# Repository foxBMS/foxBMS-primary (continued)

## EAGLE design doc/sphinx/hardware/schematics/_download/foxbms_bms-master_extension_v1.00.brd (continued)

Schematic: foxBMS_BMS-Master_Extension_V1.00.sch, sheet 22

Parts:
JP2201, JP2202: PINHD-2X12; 2X12

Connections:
+3.3V_0: JP2201.1, JP2201.3, JP2202.1, JP2202.3; also elsewhere on the board
ADC_MCU_0_CH_0: JP2202.8; also elsewhere on the board
ADC_MCU_0_CH_1: JP2202.7; also elsewhere on the board
ADC_MCU_0_CH_2: JP2202.6; also elsewhere on the board
ADC_MCU_0_CH_3: JP2202.5; also elsewhere on the board
ADC_MCU_0_CH_4: JP2202.9; also elsewhere on the board
CAN_1_RX: JP2201.6; also elsewhere on the board
CAN_1_TRANS_STANDBY_CONTROL: JP2201.5; also elsewhere on the board
CAN_1_TX: JP2201.7; also elsewhere on the board
CONTACTOR_6_CONTROL: JP2201.18; also elsewhere on the board
CONTACTOR_6_FEEDBACK: JP2201.17; also elsewhere on the board
CONTACTOR_7_CONTROL: JP2201.16; also elsewhere on the board
CONTACTOR_7_FEEDBACK: JP2201.15; also elsewhere on the board
CONTACTOR_8_CONTROL: JP2202.10; also elsewhere on the board
CONTACTOR_8_FEEDBACK: JP2202.11; also elsewhere on the board
DATA_STORAGE_SPI_MISO: JP2201.21; also elsewhere on the board
DATA_STORAGE_SPI_MOSI: JP2201.19; also elsewhere on the board
DATA_STORAGE_SPI_SCK: JP2201.20; also elsewhere on the board
DATA_STORAGE_SPI_SDCARD_NSS: JP2201.23; also elsewhere on the board
GND_0: JP2201.2, JP2201.4, JP2202.2, JP2202.4; also elsewhere on the board
ISONOC_0_CONTROL: JP2202.16; also elsewhere on the board
ISONOC_1_CONTROL: JP2202.17; also elsewhere on the board
ISONOC_2_CONTROL: JP2202.18; also elsewhere on the board
ISONOC_3_CONTROL: JP2202.19; also elsewhere on the board
ISONOC_4_CONTROL: JP2202.20; also elsewhere on the board
ISONOC_5_CONTROL: JP2202.21; also elsewhere on the board
ISO_GPIO_MCU_0_IN_0: JP2202.22; also elsewhere on the board
ISO_GPIO_MCU_0_IN_1: JP2202.23; also elsewhere on the board
ISO_GPIO_MCU_0_IN_2: JP2201.13; also elsewhere on the board
ISO_GPIO_MCU_0_IN_3: JP2201.10; also elsewhere on the board
ISO_GPIO_MCU_0_OUT_0: JP2201.9; also elsewhere on the board
ISO_GPIO_MCU_0_OUT_1: JP2201.14; also elsewhere on the board
ISO_GPIO_MCU_0_OUT_2: JP2201.11; also elsewhere on the board
ISO_GPIO_MCU_0_OUT_3: JP2201.12; also elsewhere on the board
RS485_MCU_0_DE: JP2202.15; also elsewhere on the board
RS485_MCU_0_NRE: JP2202.14; also elsewhere on the board
RS485_MCU_0_RX: JP2202.13; also elsewhere on the board
RS485_MCU_0_TX: JP2202.12; also elsewhere on the board
SDCARD_SUPPLY_CONTROL: JP2201.22; also elsewhere on the board

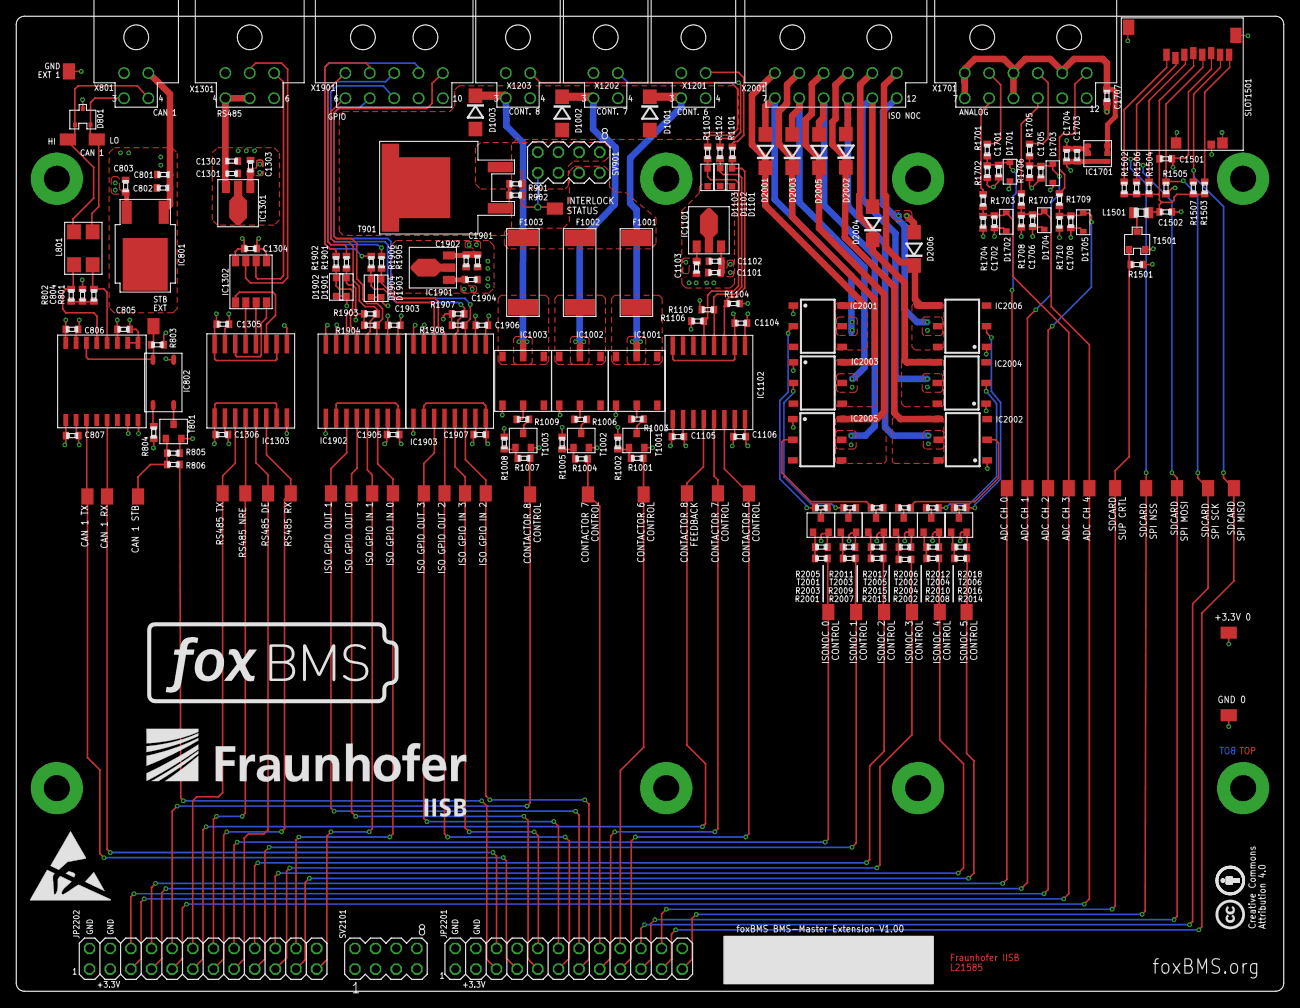
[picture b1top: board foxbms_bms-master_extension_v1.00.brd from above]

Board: 4 copper layers, 156.0 x 120.0 mm, 220 parts (0 on the bottom side), 141 nets.

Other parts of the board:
U$1: ESD_10.00

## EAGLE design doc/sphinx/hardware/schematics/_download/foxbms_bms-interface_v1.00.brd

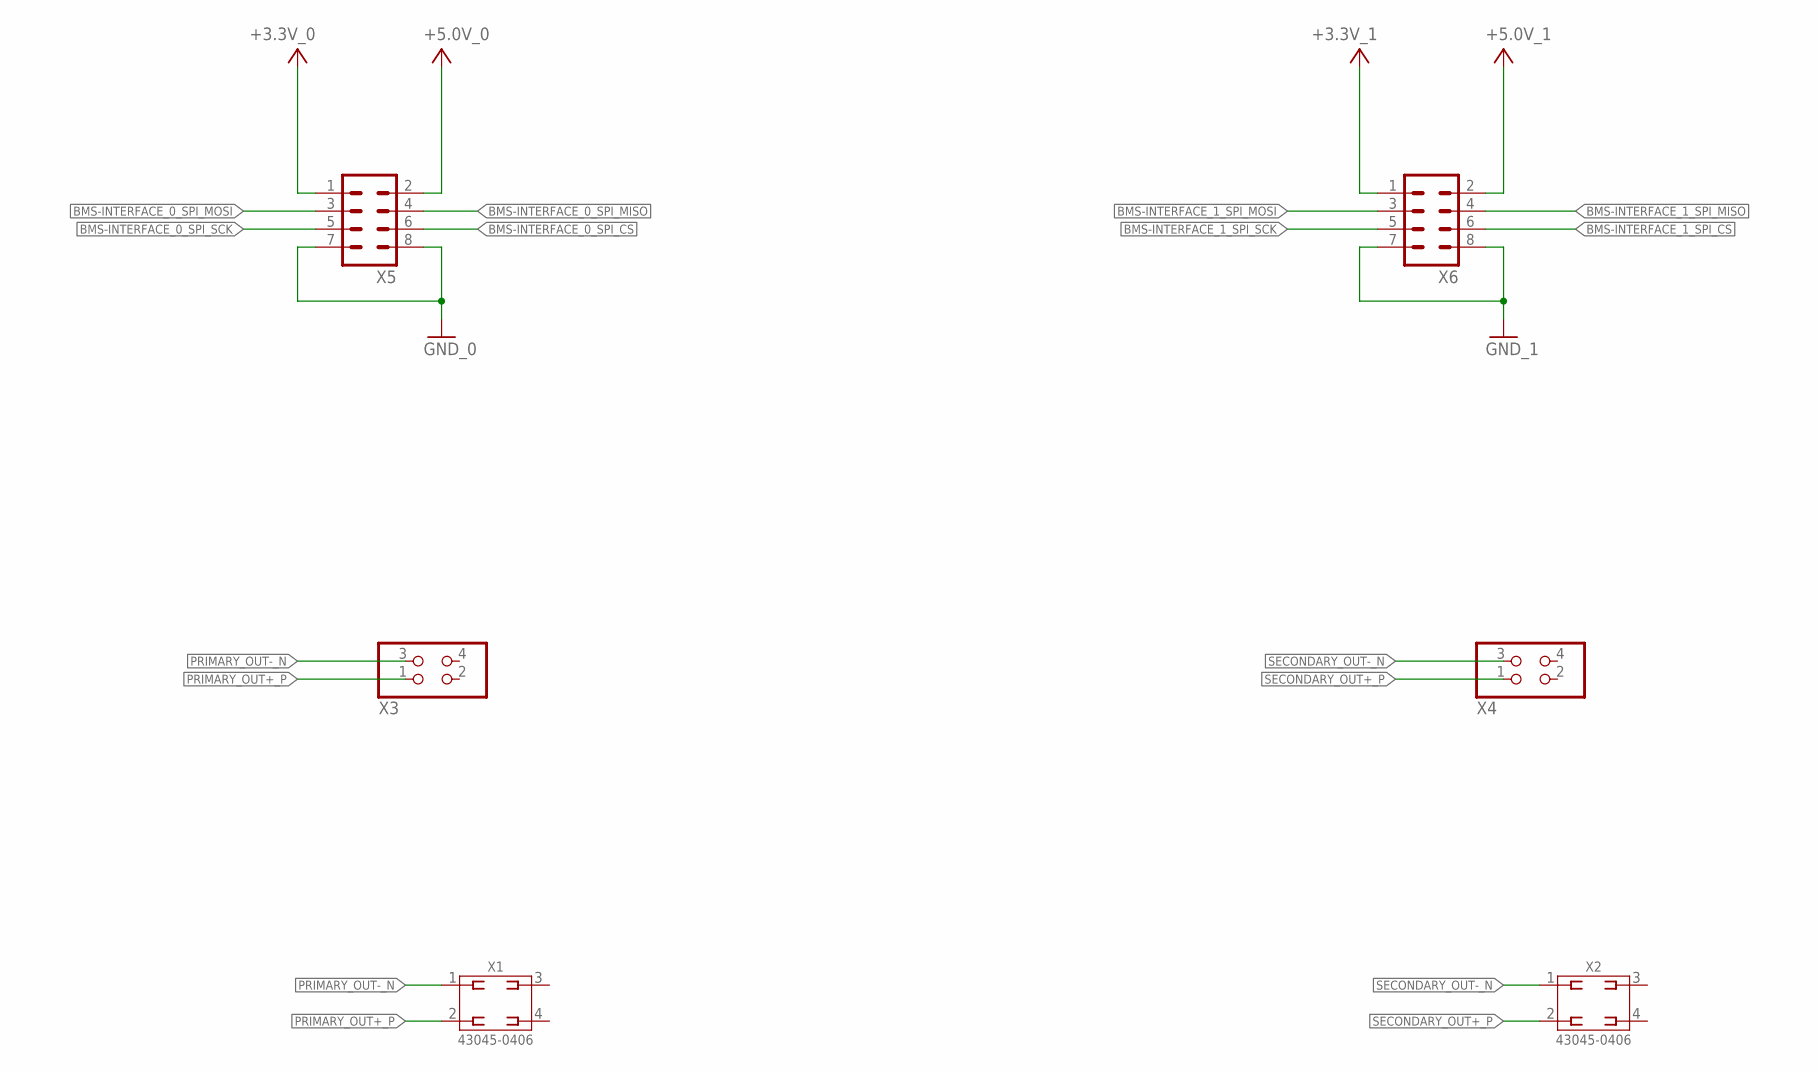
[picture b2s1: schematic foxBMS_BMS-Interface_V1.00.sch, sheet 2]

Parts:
X1, X2: 43045-0406_MOLEX_4PIN; X_SMD_MOLEX_43045-0408_R_REV01
X3, X4: PINHD-2X2; 2X02
X5, X6: MA04-2

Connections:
+3.3V_0: X5.1; also elsewhere on the board
+3.3V_1: X6.1; also elsewhere on the board
+5.0V_0: X5.2
+5.0V_1: X6.2
BMS-INTERFACE_0_SPI_CS: X5.6; also elsewhere on the board
BMS-INTERFACE_0_SPI_MISO: X5.4; also elsewhere on the board
BMS-INTERFACE_0_SPI_MOSI: X5.3; also elsewhere on the board
BMS-INTERFACE_0_SPI_SCK: X5.5; also elsewhere on the board
BMS-INTERFACE_1_SPI_CS: X6.6; also elsewhere on the board
BMS-INTERFACE_1_SPI_MISO: X6.4; also elsewhere on the board
BMS-INTERFACE_1_SPI_MOSI: X6.3; also elsewhere on the board
BMS-INTERFACE_1_SPI_SCK: X6.5; also elsewhere on the board
GND_0: X5.7, X5.8; also elsewhere on the board
GND_1: X6.7, X6.8; also elsewhere on the board
PRIMARY_OUT+_P: X1.2, X3.1; also elsewhere on the board
PRIMARY_OUT-_N: X1.1, X3.3; also elsewhere on the board
SECONDARY_OUT+_P: X2.2, X4.1; also elsewhere on the board
SECONDARY_OUT-_N: X2.1, X4.3; also elsewhere on the board

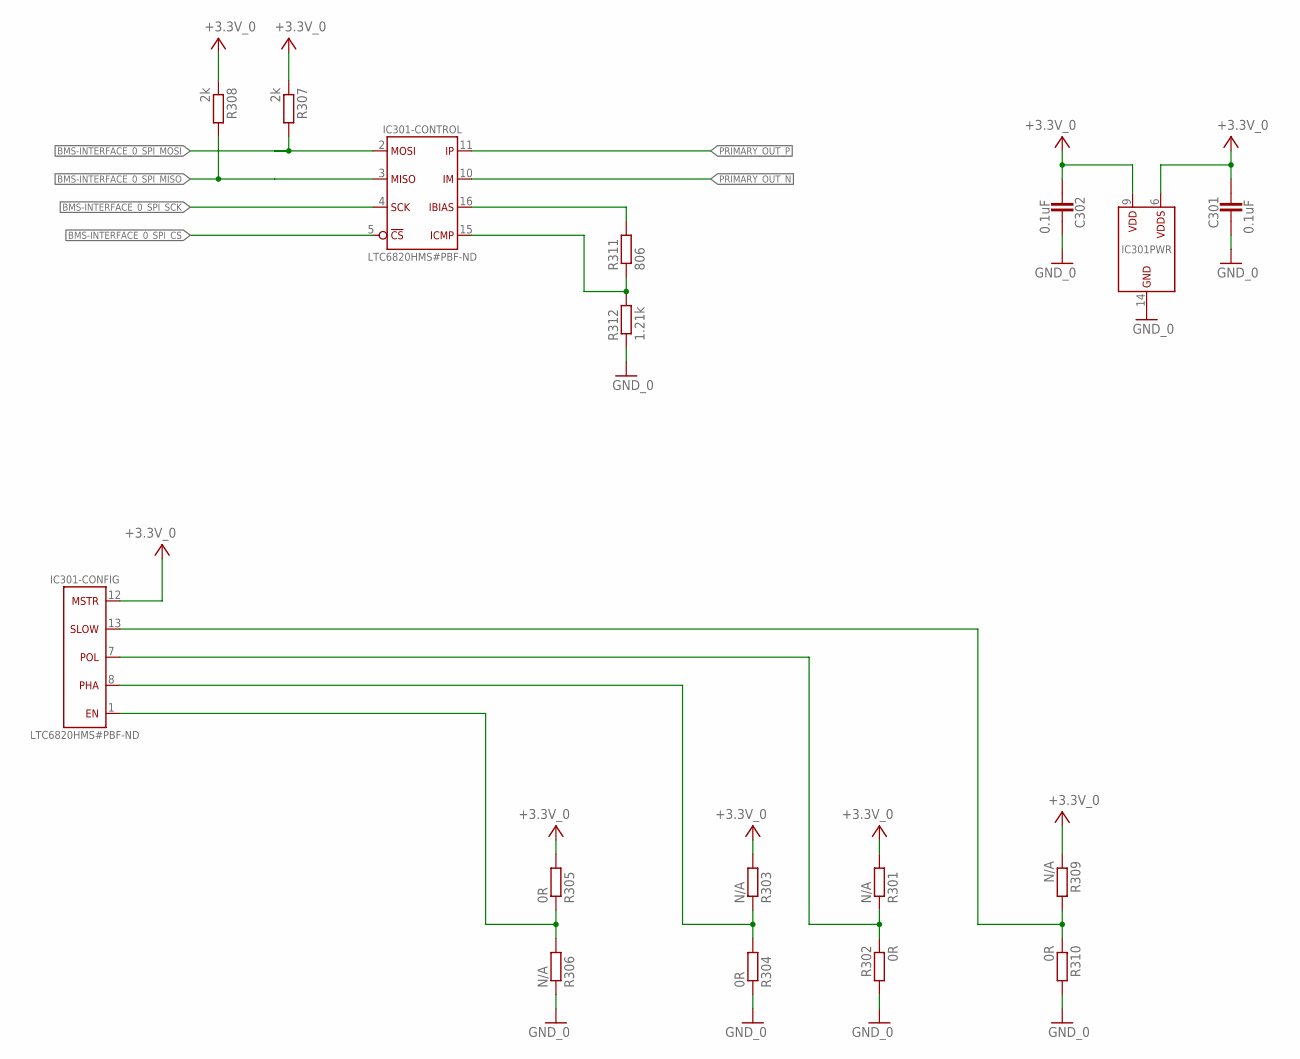
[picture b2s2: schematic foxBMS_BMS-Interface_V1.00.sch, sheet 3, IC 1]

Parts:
C301, C302: 0.1uF; 0603
IC301: LTC6820HMS#PBF; IC_SMD_MSOP-16_(MS16)_R_LINEAR_REV01
R301, R303, R306, R309: N/A; 0603
R302, R304, R305, R310: 0R; 0603
R307, R308: 2k; 0603
R311: 806; 0603
R312: 1.21k; 0603

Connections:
+3.3V_0: C301.2, C302.2, IC301.6 (VDDS), IC301.9 (VDD), IC301.12 (MSTR), R301.2, R303.2, R305.2, R307.1, R308.1, R309.1; also elsewhere on the board
BMS-INTERFACE_0_SPI_CS: IC301.5 (!CS); also elsewhere on the board
BMS-INTERFACE_0_SPI_MISO: IC301.3 (MISO), R308.2; also elsewhere on the board
BMS-INTERFACE_0_SPI_MOSI: IC301.2 (MOSI), R307.2; also elsewhere on the board
BMS-INTERFACE_0_SPI_SCK: IC301.4 (SCK); also elsewhere on the board
EN-BACKUP: IC301.1 (EN), R305.1, R306.2
GND_0: C301.1, C302.1, IC301.14 (GND), R302.2, R304.1, R306.1, R310.2, R312.1; also elsewhere on the board
unnamed: IC301.16 (IBIAS), R311.2
unnamed: IC301.15 (ICMP), R311.1, R312.2
PHA-PRIMARY: IC301.8 (PHA), R303.1, R304.2
POL-PRIMARY: IC301.7 (POL), R301.1, R302.1
PRIMARY_OUT_N: IC301.10 (IM); also elsewhere on the board
PRIMARY_OUT_P: IC301.11 (IP); also elsewhere on the board
SLOW-PRIMARY: IC301.13 (SLOW), R309.2, R310.1

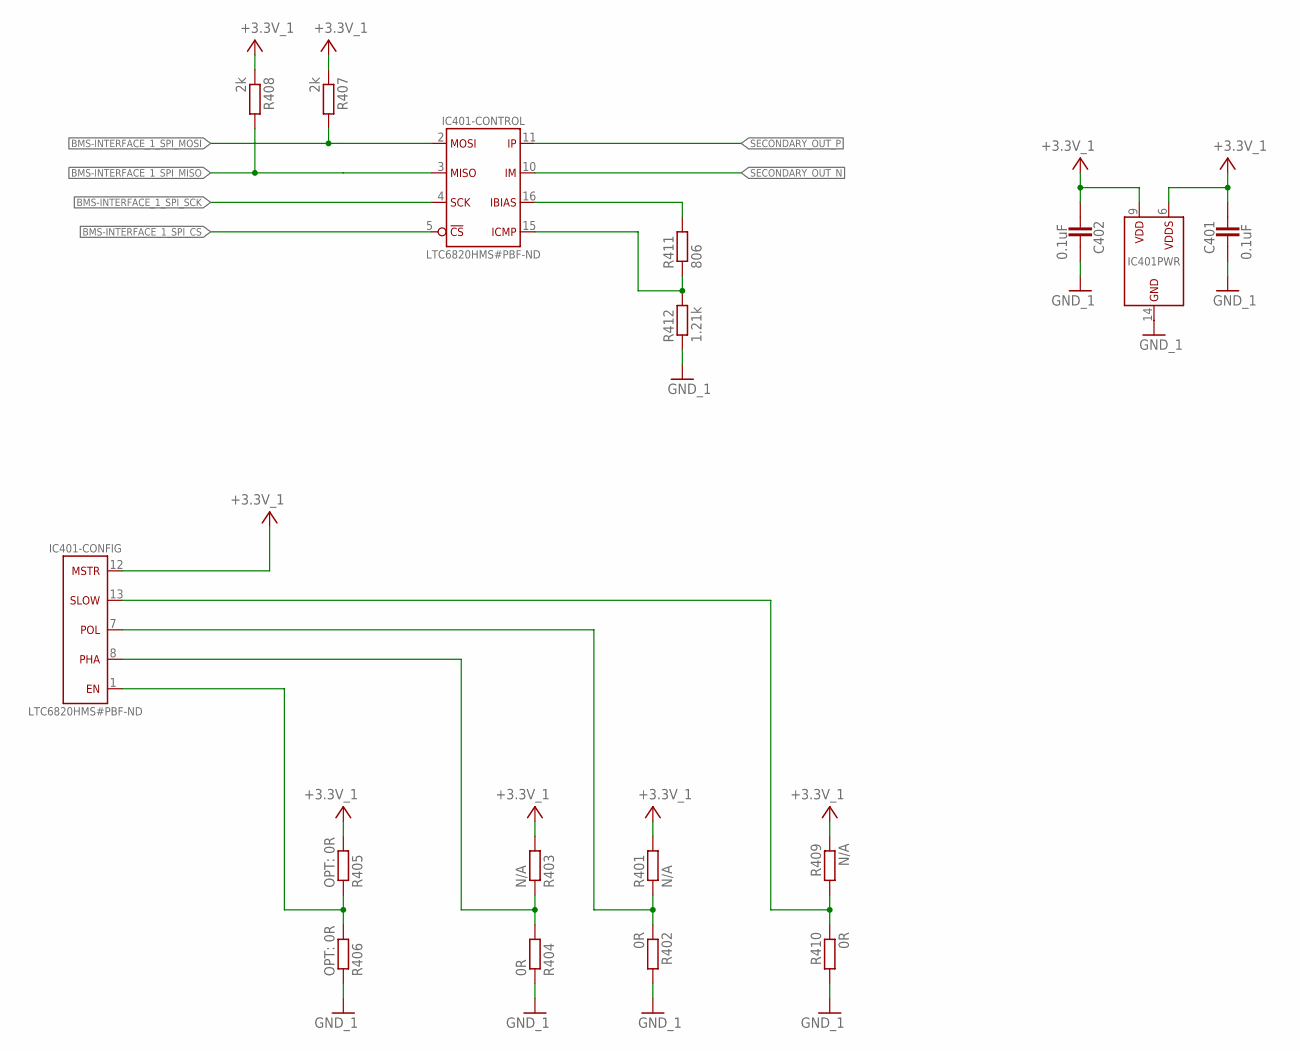
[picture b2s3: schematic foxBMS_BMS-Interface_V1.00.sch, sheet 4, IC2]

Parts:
C401, C402: 0.1uF; 0603
IC401: LTC6820HMS#PBF; IC_SMD_MSOP-16_(MS16)_R_LINEAR_REV01
R401, R403, R409: N/A; 0603
R402, R404, R410: 0R; 0603
R405, R406: OPT: 0R; 0603
R407, R408: 2k; 0603
R411: 806; 0603
R412: 1.21k; 0603

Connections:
+3.3V_1: C401.2, C402.2, IC401.6 (VDDS), IC401.9 (VDD), IC401.12 (MSTR), R401.2, R403.2, R405.2, R407.1, R408.1, R409.1; also elsewhere on the board
BMS-INTERFACE_1_SPI_CS: IC401.5 (!CS); also elsewhere on the board
BMS-INTERFACE_1_SPI_MISO: IC401.3 (MISO), R408.2; also elsewhere on the board
BMS-INTERFACE_1_SPI_MOSI: IC401.2 (MOSI), R407.2; also elsewhere on the board
BMS-INTERFACE_1_SPI_SCK: IC401.4 (SCK); also elsewhere on the board
EN-BACKUP1: IC401.1 (EN), R405.1, R406.2
GND_1: C401.1, C402.1, IC401.14 (GND), R402.2, R404.1, R406.1, R410.2, R412.1; also elsewhere on the board
unnamed: IC401.15 (ICMP), R411.1, R412.2
unnamed: IC401.16 (IBIAS), R411.2
PHA-SECONDARY: IC401.8 (PHA), R403.1, R404.2
POL-SECONDARY: IC401.7 (POL), R401.1, R402.1
SECONDARY_OUT_N: IC401.10 (IM); also elsewhere on the board
SECONDARY_OUT_P: IC401.11 (IP); also elsewhere on the board
SLOW-SECONDARY: IC401.13 (SLOW), R409.2, R410.1

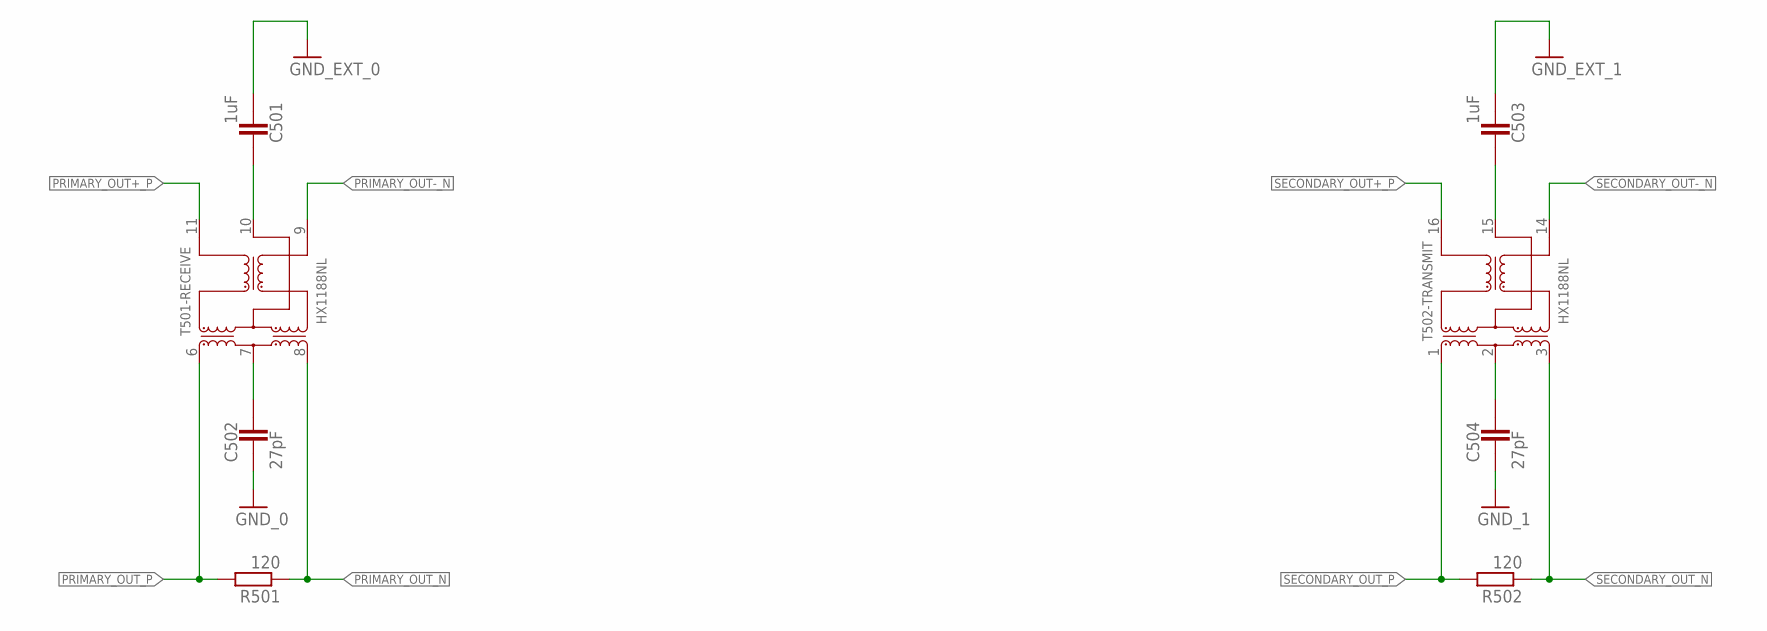
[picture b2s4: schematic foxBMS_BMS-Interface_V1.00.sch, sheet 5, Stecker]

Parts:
C501, C503: 1uF; 0603
C502, C504: 27pF; 0603
R501, R502: 120; 0603
T501, T502: HX1188NL; TR_SMD_SOIC-16_(12,70MMX9,53MMX5,97MM)_R_PULSE_REV01

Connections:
GND_0: C502.1; also elsewhere on the board
GND_1: C504.1; also elsewhere on the board
GND_EXT_0: C501.1
GND_EXT_1: C503.1
unnamed: C504.2, T502.2 (CT)
unnamed: C503.2, T502.15 (CMT)
unnamed: C502.2, T501.7 (CT)
unnamed: C501.2, T501.10 (CMT)
PRIMARY_OUT+_P: T501.11 (X+); also elsewhere on the board
PRIMARY_OUT-_N: T501.9 (X-); also elsewhere on the board
PRIMARY_OUT_N: R501.1, T501.8 (D-); also elsewhere on the board
PRIMARY_OUT_P: R501.2, T501.6 (D+); also elsewhere on the board
SECONDARY_OUT+_P: T502.16 (X+); also elsewhere on the board
SECONDARY_OUT-_N: T502.14 (X-); also elsewhere on the board
SECONDARY_OUT_N: R502.1, T502.3 (D-); also elsewhere on the board
SECONDARY_OUT_P: R502.2, T502.1 (D+); also elsewhere on the board

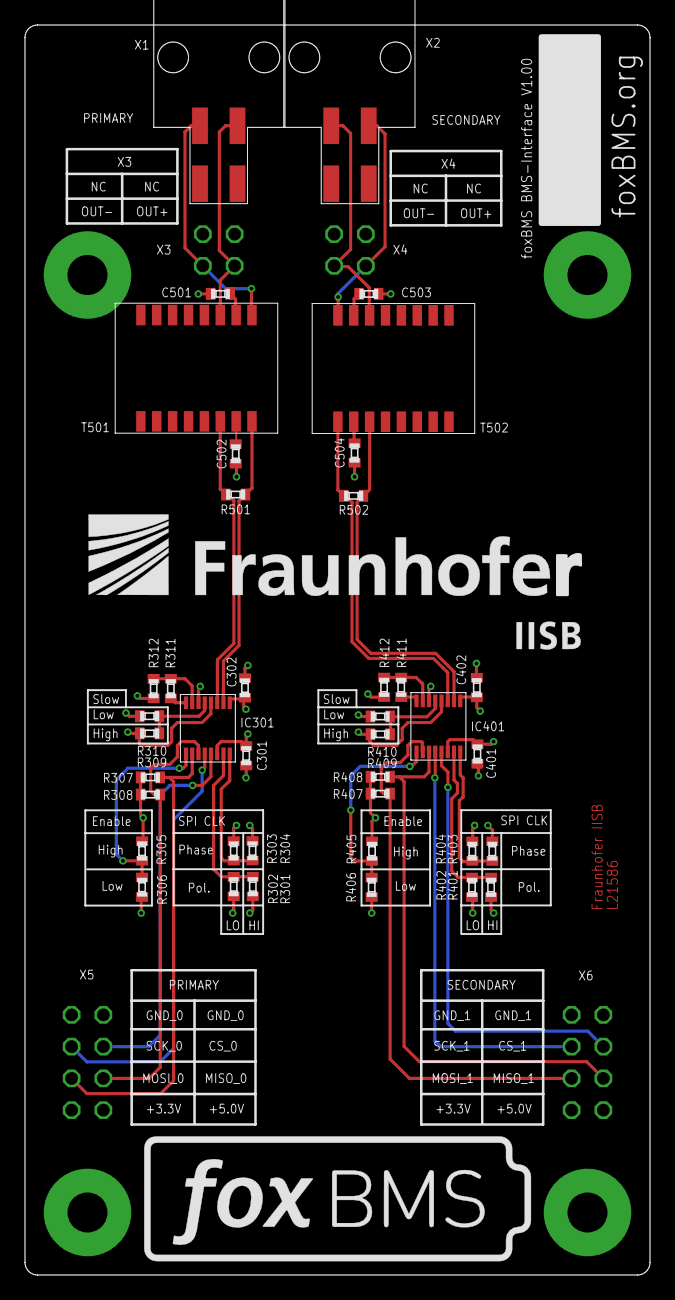
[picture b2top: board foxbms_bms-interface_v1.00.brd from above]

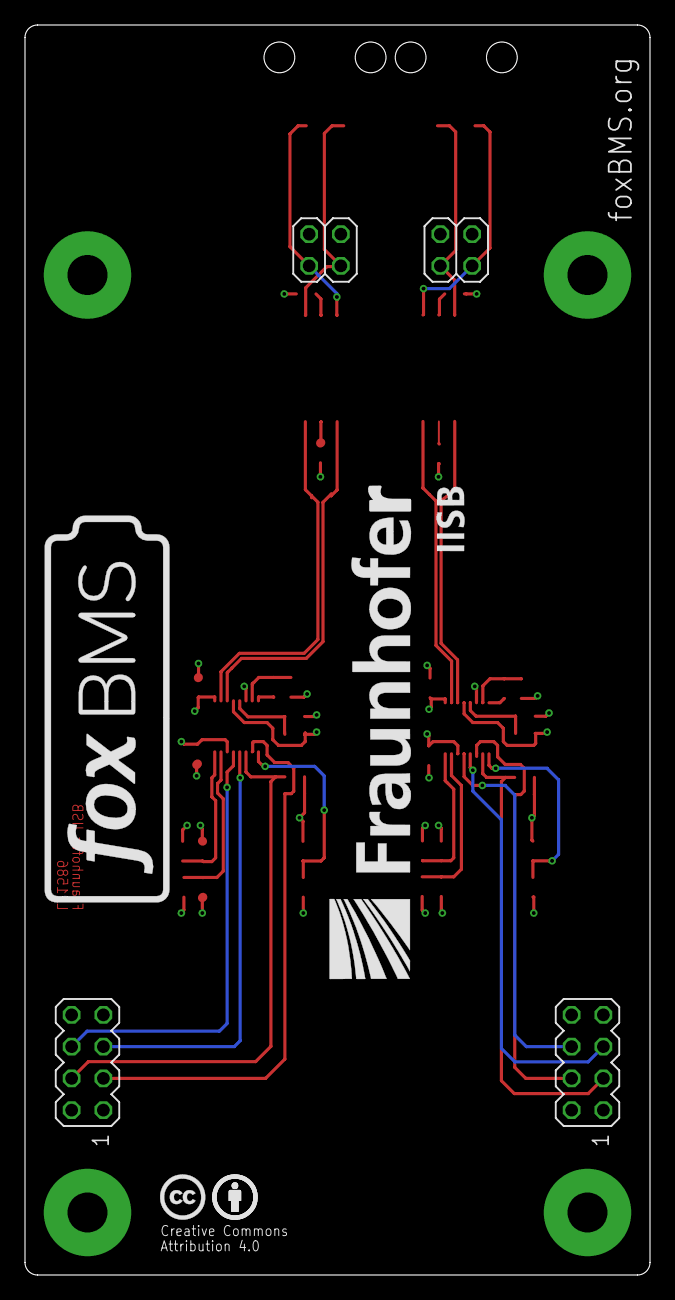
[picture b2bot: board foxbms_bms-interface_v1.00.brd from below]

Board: 4 copper layers, 50.0 x 100.0 mm, 44 parts (4 on the bottom side), 36 nets.

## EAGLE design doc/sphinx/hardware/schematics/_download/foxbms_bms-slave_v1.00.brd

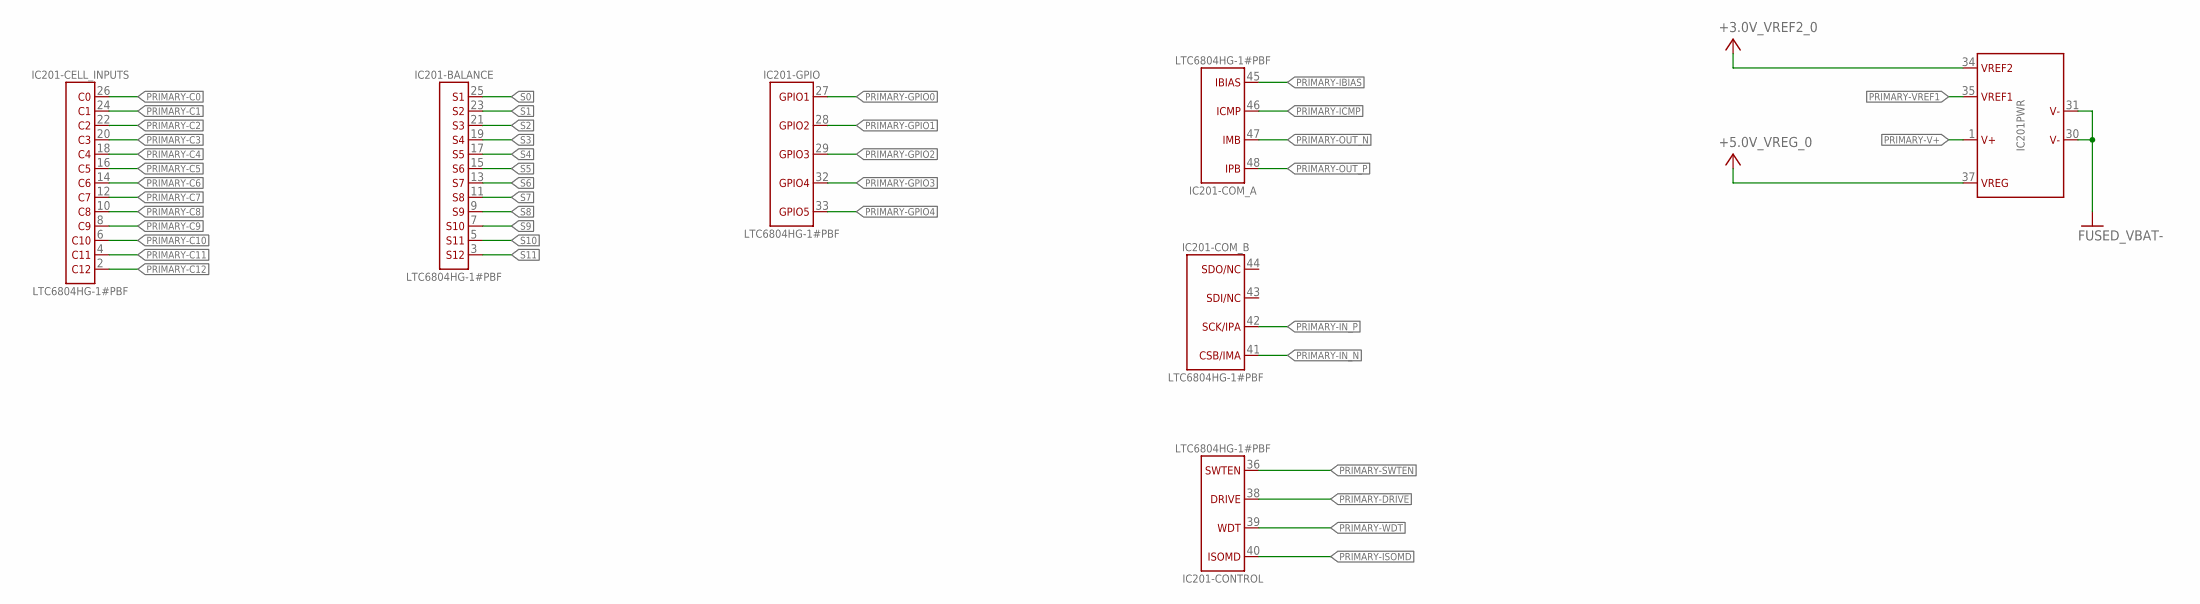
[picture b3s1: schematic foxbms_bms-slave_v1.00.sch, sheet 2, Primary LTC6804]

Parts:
IC201: LTC6804HG-1#PBF; IC_SMD_SSOP-48_(G48)_R_LINEAR_REV01

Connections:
+3.0V_VREF2_0: IC201.34 (VREF2); also elsewhere on the board
+5.0V_VREG_0: IC201.37 (VREG); also elsewhere on the board
FUSED_VBAT-: IC201.30 (V-1), IC201.31 (V-2); also elsewhere on the board
PRIMARY-C0: IC201.26 (C0); also elsewhere on the board
PRIMARY-C1: IC201.24 (C1); also elsewhere on the board
PRIMARY-C2: IC201.22 (C2); also elsewhere on the board
PRIMARY-C3: IC201.20 (C3); also elsewhere on the board
PRIMARY-C4: IC201.18 (C4); also elsewhere on the board
PRIMARY-C5: IC201.16 (C5); also elsewhere on the board
PRIMARY-C6: IC201.14 (C6); also elsewhere on the board
PRIMARY-C7: IC201.12 (C7); also elsewhere on the board
PRIMARY-C8: IC201.10 (C8); also elsewhere on the board
PRIMARY-C9: IC201.8 (C9); also elsewhere on the board
PRIMARY-C10: IC201.6 (C10); also elsewhere on the board
PRIMARY-C11: IC201.4 (C11); also elsewhere on the board
PRIMARY-C12: IC201.2 (C12); also elsewhere on the board
PRIMARY-DRIVE: IC201.38 (DRIVE); also elsewhere on the board
PRIMARY-GPIO0: IC201.27 (GPIO1); also elsewhere on the board
PRIMARY-GPIO1: IC201.28 (GPIO2); also elsewhere on the board
PRIMARY-GPIO2: IC201.29 (GPIO3); also elsewhere on the board
PRIMARY-GPIO3: IC201.32 (GPIO4); also elsewhere on the board
PRIMARY-GPIO4: IC201.33 (GPIO5); also elsewhere on the board
PRIMARY-IBIAS: IC201.45 (IBIAS); also elsewhere on the board
PRIMARY-ICMP: IC201.46 (ICMP); also elsewhere on the board
PRIMARY-IN_N: IC201.41 (CSB/IMA); also elsewhere on the board
PRIMARY-IN_P: IC201.42 (SCK/IPA); also elsewhere on the board
PRIMARY-ISOMD: IC201.40 (ISOMD); also elsewhere on the board
PRIMARY-OUT_N: IC201.47 (IMB); also elsewhere on the board
PRIMARY-OUT_P: IC201.48 (IPB); also elsewhere on the board
PRIMARY-SWTEN: IC201.36 (SWTEN); also elsewhere on the board
PRIMARY-V+: IC201.1 (V+); also elsewhere on the board
PRIMARY-VREF1: IC201.35 (VREF1); also elsewhere on the board
PRIMARY-WDT: IC201.39 (WDT); also elsewhere on the board
S0: IC201.25 (S1); also elsewhere on the board
S1: IC201.23 (S2); also elsewhere on the board
S2: IC201.21 (S3); also elsewhere on the board
S3: IC201.19 (S4); also elsewhere on the board
S4: IC201.17 (S5); also elsewhere on the board
S5: IC201.15 (S6); also elsewhere on the board
S6: IC201.13 (S7); also elsewhere on the board
S7: IC201.11 (S8); also elsewhere on the board
S8: IC201.9 (S9); also elsewhere on the board
S9: IC201.7 (S10); also elsewhere on the board
S10: IC201.5 (S11); also elsewhere on the board
S11: IC201.3 (S12); also elsewhere on the board

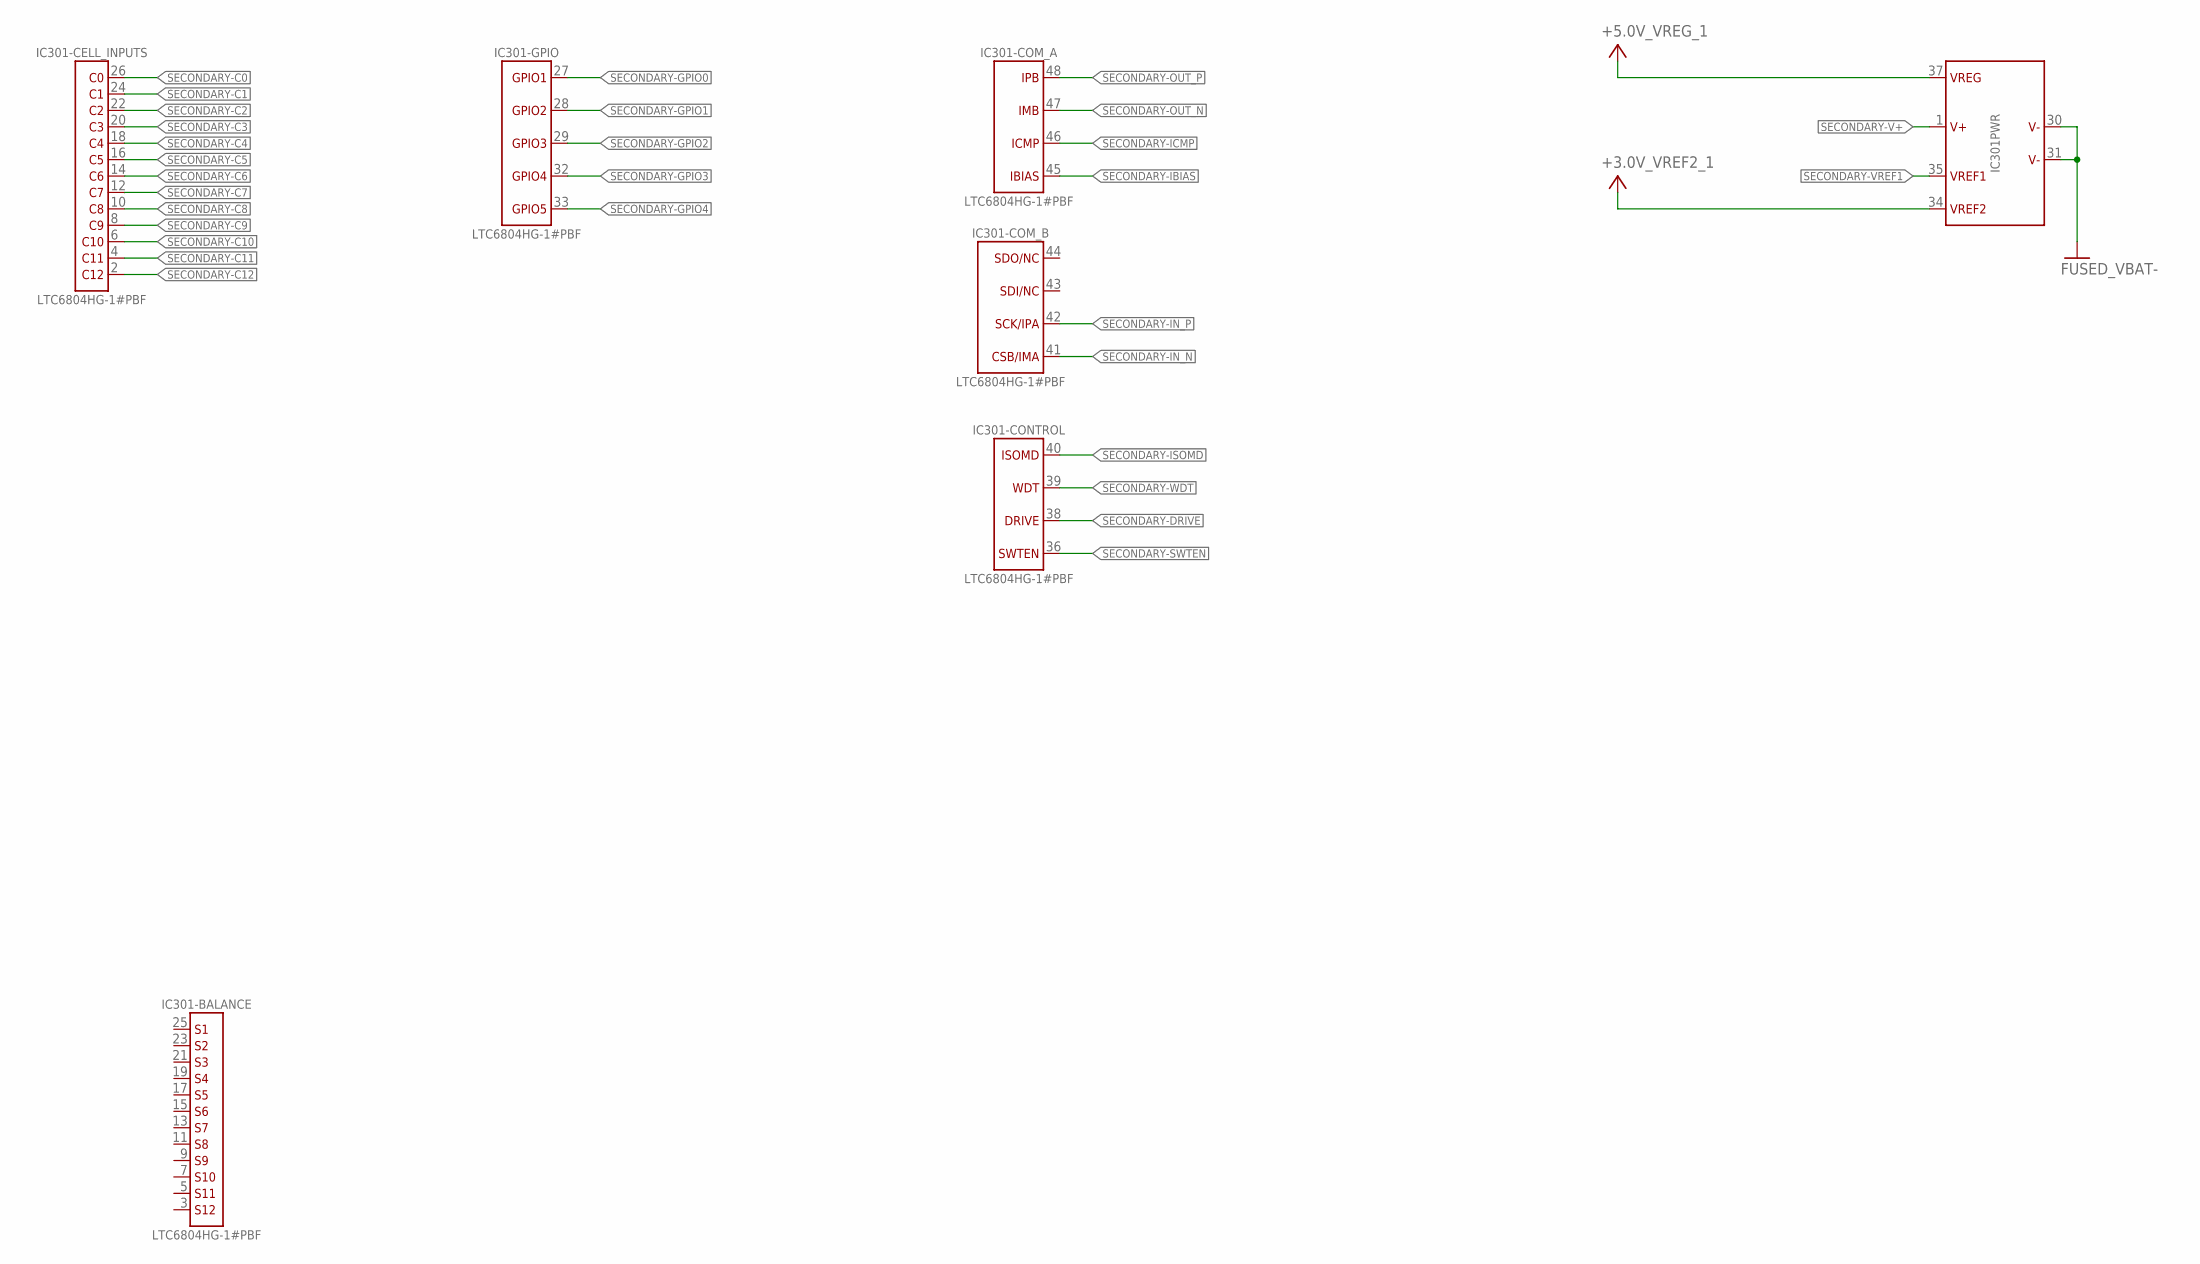
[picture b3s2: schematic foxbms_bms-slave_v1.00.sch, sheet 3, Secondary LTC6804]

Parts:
IC301: LTC6804HG-1#PBF; IC_SMD_SSOP-48_(G48)_R_LINEAR_REV01

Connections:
+3.0V_VREF2_1: IC301.34 (VREF2); also elsewhere on the board
+5.0V_VREG_1: IC301.37 (VREG); also elsewhere on the board
FUSED_VBAT-: IC301.30 (V-1), IC301.31 (V-2); also elsewhere on the board
SECONDARY-C0: IC301.26 (C0); also elsewhere on the board
SECONDARY-C1: IC301.24 (C1); also elsewhere on the board
SECONDARY-C2: IC301.22 (C2); also elsewhere on the board
SECONDARY-C3: IC301.20 (C3); also elsewhere on the board
SECONDARY-C4: IC301.18 (C4); also elsewhere on the board
SECONDARY-C5: IC301.16 (C5); also elsewhere on the board
SECONDARY-C6: IC301.14 (C6); also elsewhere on the board
SECONDARY-C7: IC301.12 (C7); also elsewhere on the board
SECONDARY-C8: IC301.10 (C8); also elsewhere on the board
SECONDARY-C9: IC301.8 (C9); also elsewhere on the board
SECONDARY-C10: IC301.6 (C10); also elsewhere on the board
SECONDARY-C11: IC301.4 (C11); also elsewhere on the board
SECONDARY-C12: IC301.2 (C12); also elsewhere on the board
SECONDARY-DRIVE: IC301.38 (DRIVE); also elsewhere on the board
SECONDARY-GPIO0: IC301.27 (GPIO1); also elsewhere on the board
SECONDARY-GPIO1: IC301.28 (GPIO2); also elsewhere on the board
SECONDARY-GPIO2: IC301.29 (GPIO3); also elsewhere on the board
SECONDARY-GPIO3: IC301.32 (GPIO4); also elsewhere on the board
SECONDARY-GPIO4: IC301.33 (GPIO5); also elsewhere on the board
SECONDARY-IBIAS: IC301.45 (IBIAS); also elsewhere on the board
SECONDARY-ICMP: IC301.46 (ICMP); also elsewhere on the board
SECONDARY-IN_N: IC301.41 (CSB/IMA); also elsewhere on the board
SECONDARY-IN_P: IC301.42 (SCK/IPA); also elsewhere on the board
SECONDARY-ISOMD: IC301.40 (ISOMD); also elsewhere on the board
SECONDARY-OUT_N: IC301.47 (IMB); also elsewhere on the board
SECONDARY-OUT_P: IC301.48 (IPB); also elsewhere on the board
SECONDARY-SWTEN: IC301.36 (SWTEN); also elsewhere on the board
SECONDARY-V+: IC301.1 (V+); also elsewhere on the board
SECONDARY-VREF1: IC301.35 (VREF1); also elsewhere on the board
SECONDARY-WDT: IC301.39 (WDT); also elsewhere on the board

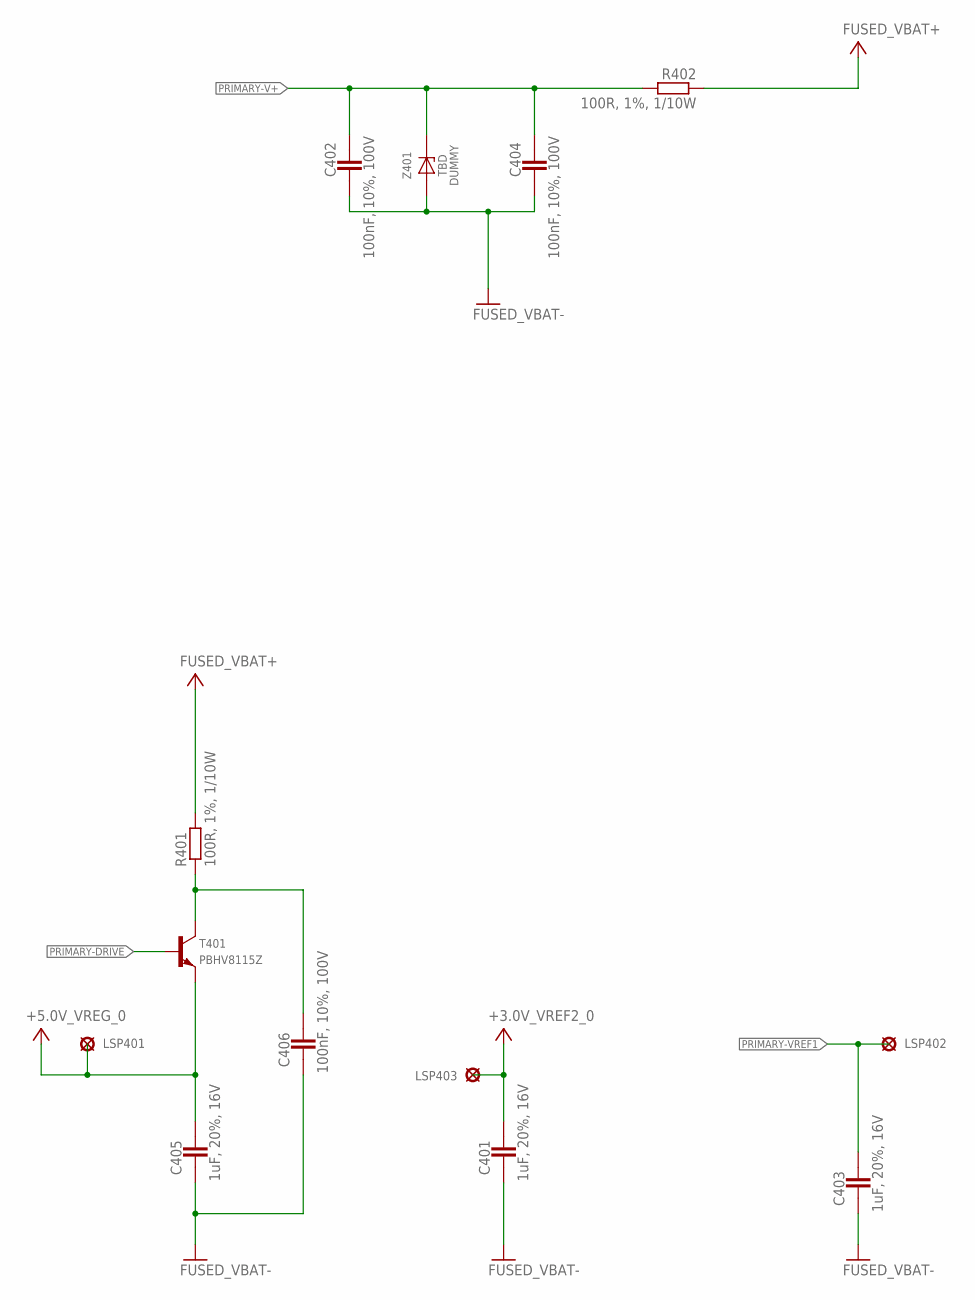
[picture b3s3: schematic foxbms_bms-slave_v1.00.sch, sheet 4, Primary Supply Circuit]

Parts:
C401, C403, C405: 1uF, 20%, 16V; 0603
C402, C404, C406: 100nF, 10%, 100V; 0805
LSP401, LSP402, LSP403: PAD_2.0X1.5MM; PAD2.0X1.5MM
R401, R402: 100R, 1%, 1/10W; 0603
T401: PBHV8115Z; D_SMD_SOT223_(SC-73)_R_NXP_REV01
Z401: 60V,500mW; D_SMD_SOD-123_R_ON_REV01

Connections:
+3.0V_VREF2_0: C401.2, LSP403.P$1; also elsewhere on the board
+5.0V_VREG_0: C405.2, LSP401.P$1, T401.3 (E); also elsewhere on the board
FUSED_VBAT+: R401.2, R402.1; also elsewhere on the board
FUSED_VBAT-: C401.1, C402.2, C403.1, C404.2, C405.1, C406.1, Z401.A; also elsewhere on the board
unnamed: C406.2, R401.1, T401.2 (C), T401.4 (C)
PRIMARY-DRIVE: T401.1 (B); also elsewhere on the board
PRIMARY-V+: C402.1, C404.1, R402.2, Z401.K (C); also elsewhere on the board
PRIMARY-VREF1: C403.2, LSP402.P$1; also elsewhere on the board
